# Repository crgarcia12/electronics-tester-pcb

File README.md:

# electronics-tester-pcb
A PCB to test fabrication

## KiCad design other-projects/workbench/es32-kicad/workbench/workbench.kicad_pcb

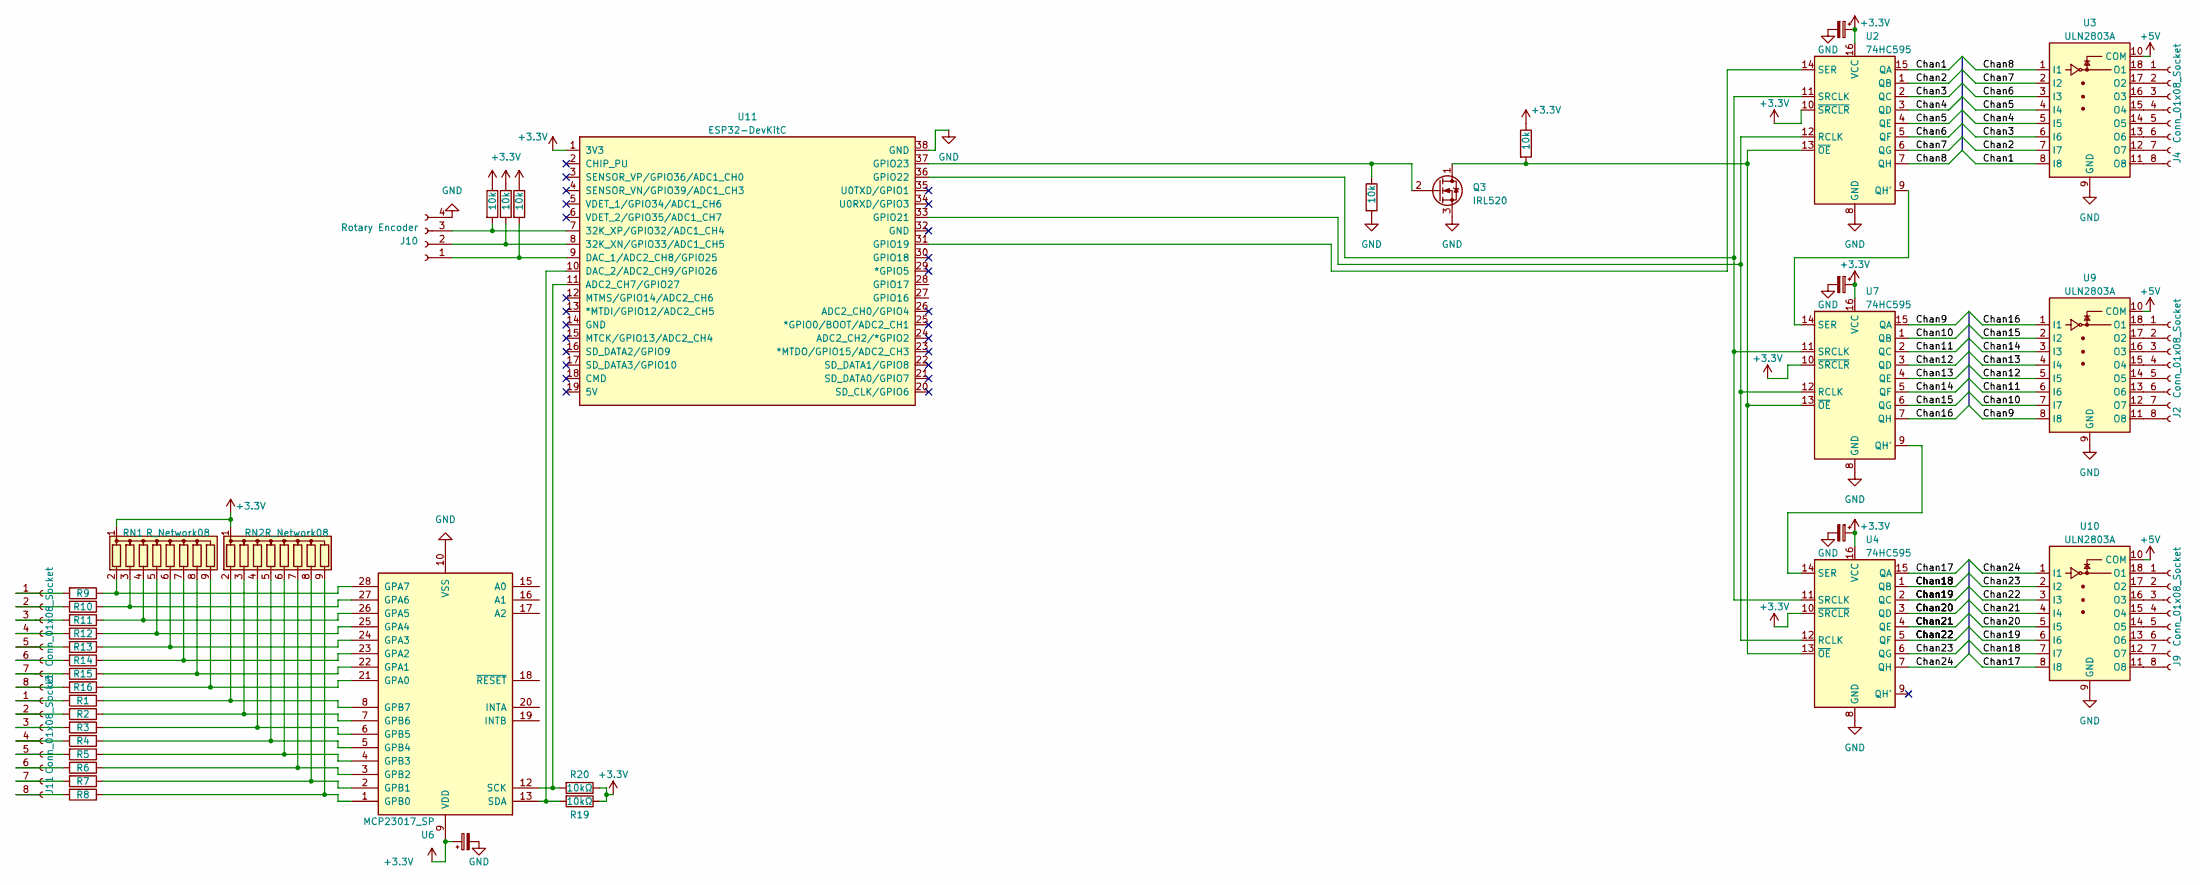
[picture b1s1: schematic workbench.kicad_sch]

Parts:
C14, C15, C16, C17: 10uF; CP_Radial_D6.3mm_P2.50mm
J2, J3, J4, J9, J11: Conn_01x08_Socket; PinSocket_1x08_P2.54mm_Vertical
J10: Rotary Encoder; JST_EH_B4B-EH-A_1x04_P2.50mm_Vertical
Q3: IRL520; TO-220-3_Vertical
R1, R2, R3, R4, R5, R6, R7, R8, R9, R10, R11, R12, R13, R14, R15, R16: R; R_Axial_DIN0207_L6.3mm_D2.5mm_P7.62mm_Horizontal
R19, R20: 10kΩ; R_Axial_DIN0207_L6.3mm_D2.5mm_P7.62mm_Horizontal; JLCPCB C25804
R21, R22, R35, R52, R53: 10k; R_Axial_DIN0207_L6.3mm_D2.5mm_P7.62mm_Horizontal
RN1, RN2: R_Network08; R_Array_SIP9
U2, U4, U7: 74HC595; DIP-16_W7.62mm_Socket_LongPads
U3, U9, U10: ULN2803A; DIP-18_W7.62mm_LongPads
U6: MCP23017_SP; DIP-28_W7.62mm
U11: ESP32-DevKitC

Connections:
+3.3V: C14.1, C15.1, C16.1, C17.1, R19.1, R20.1, R21.1, R22.1, R35.1, R53.1, RN1.1 (common), RN2.1 (common), U2.10 (~SRCLR), U2.16 (VCC), U4.10 (~SRCLR), U4.16 (VCC), U6.9 (VDD), U7.10 (~SRCLR), U7.16 (VCC), U11.1 (3V3)
+5V: U3.10 (COM), U9.10 (COM), U10.10 (COM)
/Chan1: U2.15 (QA), U3.8 (I8)
/Chan2: U2.1 (QB), U3.7 (I7)
/Chan3: U2.2 (QC), U3.6 (I6)
/Chan4: U2.3 (QD), U3.5 (I5)
/Chan5: U2.4 (QE), U3.4 (I4)
/Chan6: U2.5 (QF), U3.3 (I3)
/Chan7: U2.6 (QG), U3.2 (I2)
/Chan8: U2.7 (QH), U3.1 (I1)
/Chan9: U7.15 (QA), U9.8 (I8)
/Chan10: U7.1 (QB), U9.7 (I7)
/Chan11: U7.2 (QC), U9.6 (I6)
/Chan12: U7.3 (QD), U9.5 (I5)
/Chan13: U7.4 (QE), U9.4 (I4)
/Chan14: U7.5 (QF), U9.3 (I3)
/Chan15: U7.6 (QG), U9.2 (I2)
/Chan16: U7.7 (QH), U9.1 (I1)
/Chan17: U4.15 (QA), U10.8 (I8)
/Chan18: U4.1 (QB), U10.7 (I7)
/Chan19: U4.2 (QC), U10.6 (I6)
/Chan20: U4.3 (QD), U10.5 (I5)
/Chan21: U4.4 (QE), U10.4 (I4)
/Chan22: U4.5 (QF), U10.3 (I3)
/Chan23: U4.6 (QG), U10.2 (I2)
/Chan24: U4.7 (QH), U10.1 (I1)
GND: C14.2, C15.2, C16.2, C17.2, J10.4, Q3.3 (S), R52.2, U2.8 (GND), U3.9 (GND), U4.8 (GND), U6.10 (VSS), U7.8 (GND), U9.9 (GND), U10.9 (GND), U11.38 (GND)
unnamed: J2.1, U9.18 (O1)
unnamed: J2.2, U9.17 (O2)
unnamed: J2.3, U9.16 (O3)
unnamed: J2.4, U9.15 (O4)
unnamed: J2.5, U9.14 (O5)
unnamed: J2.6, U9.13 (O6)
unnamed: J2.7, U9.12 (O7)
unnamed: J2.8, U9.11 (O8)
unnamed: J3.1, R9.2
unnamed: J3.2, R10.2
unnamed: J3.3, R11.2
unnamed: J3.4, R12.2
unnamed: J3.5, R13.2
unnamed: J3.6, R14.2
unnamed: J3.7, R15.2
unnamed: J3.8, R16.2
unnamed: J4.1, U3.18 (O1)
unnamed: J4.2, U3.17 (O2)
unnamed: J4.3, U3.16 (O3)
unnamed: J4.4, U3.15 (O4)
unnamed: J4.5, U3.14 (O5)
unnamed: J4.6, U3.13 (O6)
unnamed: J4.7, U3.12 (O7)
unnamed: J4.8, U3.11 (O8)
unnamed: J9.1, U10.18 (O1)
unnamed: J9.2, U10.17 (O2)
unnamed: J9.3, U10.16 (O3)
unnamed: J9.4, U10.15 (O4)
unnamed: J9.5, U10.14 (O5)
unnamed: J9.6, U10.13 (O6)
unnamed: J9.7, U10.12 (O7)
unnamed: J9.8, U10.11 (O8)
unnamed: J10.1, R35.2, U11.9 (DAC_1/ADC2_CH8/GPIO25)
unnamed: J10.2, R22.2, U11.8 (32K_XN/GPIO33/ADC1_CH5)
unnamed: J10.3, R21.2, U11.7 (32K_XP/GPIO32/ADC1_CH4)
unnamed: J11.1, R1.2
unnamed: J11.2, R2.2
unnamed: J11.3, R3.2
unnamed: J11.4, R4.2
unnamed: J11.5, R5.2
unnamed: J11.6, R6.2
unnamed: J11.7, R7.2
unnamed: J11.8, R8.2
unnamed: Q3.1 (D), R53.2, U2.13 (~OE), U4.13 (~OE), U7.13 (~OE)
unnamed: Q3.2 (G), R52.1, U11.37 (GPIO23)
unnamed: R9.1, RN1.2 (R1), U6.28 (GPA7)
unnamed: R10.1, RN1.3 (R2), U6.27 (GPA6)
unnamed: R11.1, RN1.4 (R3), U6.26 (GPA5)
unnamed: R12.1, RN1.5 (R4), U6.25 (GPA4)
unnamed: R13.1, RN1.6 (R5), U6.24 (GPA3)
unnamed: R14.1, RN1.7 (R6), U6.23 (GPA2)
unnamed: R15.1, RN1.8 (R7), U6.22 (GPA1)
unnamed: R16.1, RN1.9 (R8), U6.21 (GPA0)
unnamed: R1.1, RN2.2 (R1), U6.8 (GPB7)
unnamed: R2.1, RN2.3 (R2), U6.7 (GPB6)
unnamed: R3.1, RN2.4 (R3), U6.6 (GPB5)
unnamed: R4.1, RN2.5 (R4), U6.5 (GPB4)
unnamed: R5.1, RN2.6 (R5), U6.4 (GPB3)
unnamed: R6.1, RN2.7 (R6), U6.3 (GPB2)
unnamed: R7.1, RN2.8 (R7), U6.2 (GPB1)
unnamed: R8.1, RN2.9 (R8), U6.1 (GPB0)
unnamed: U2.9 (QH'), U7.14 (SER)
unnamed: U4.14 (SER), U7.9 (QH')
unnamed: R20.2, U6.12 (SCK), U11.11 (ADC2_CH7/GPIO27)
unnamed: R19.2, U6.13 (SDA), U11.10 (DAC_2/ADC2_CH9/GPIO26)
unnamed: U2.14 (SER), U11.31 (GPIO19)
unnamed: U2.12 (RCLK), U4.12 (RCLK), U7.12 (RCLK), U11.33 (GPIO21)
unnamed: U2.11 (SRCLK), U4.11 (SRCLK), U7.11 (SRCLK), U11.36 (GPIO22)

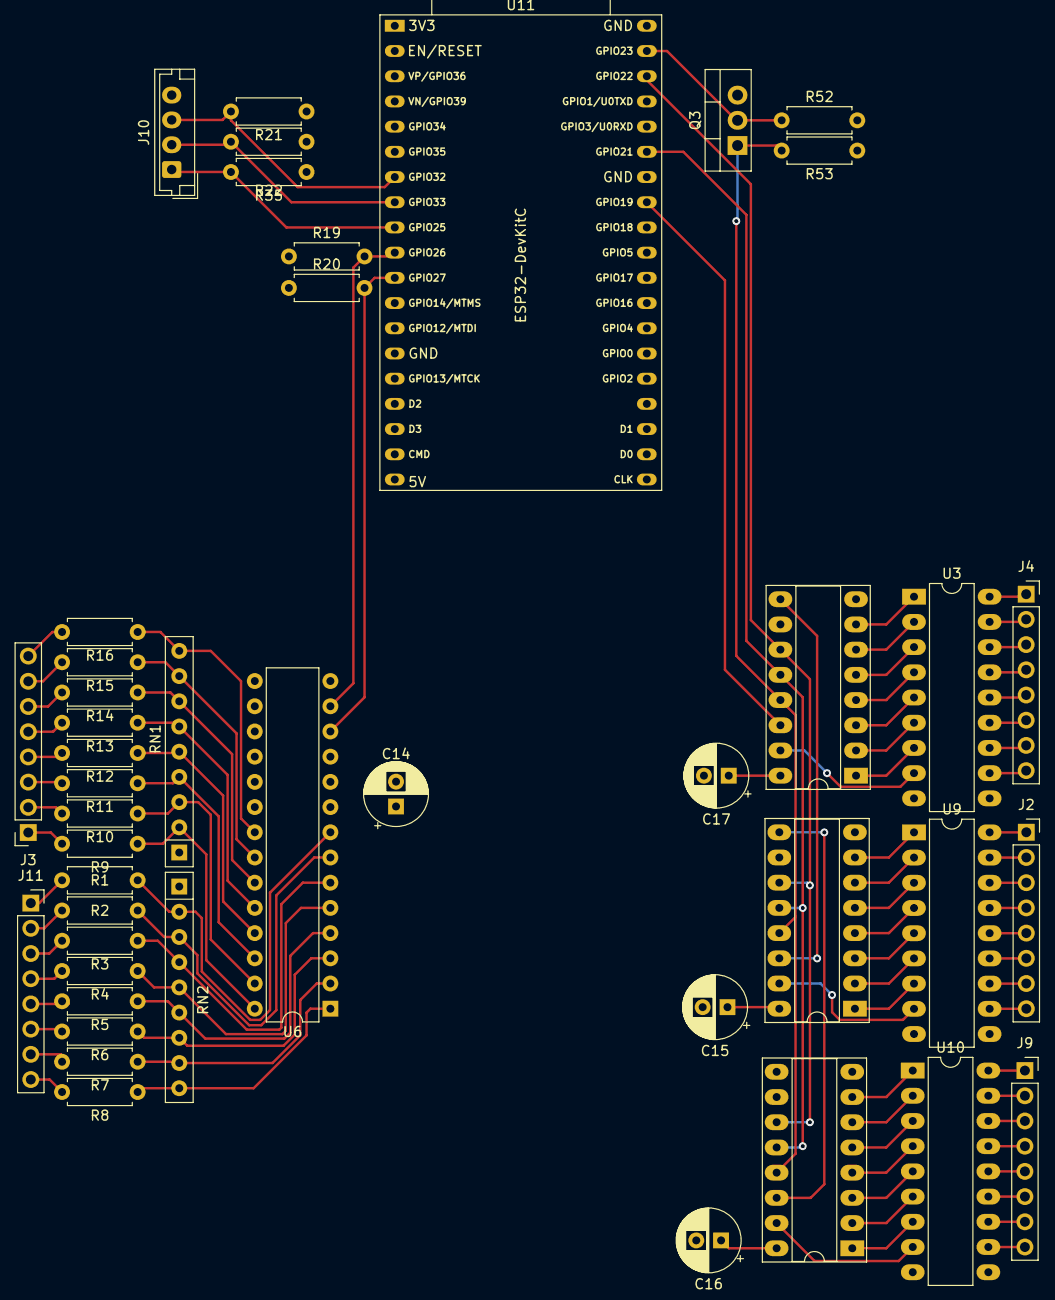
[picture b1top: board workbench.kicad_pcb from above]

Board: 4 copper layers, 44 parts (0 on the bottom side), 95 nets.

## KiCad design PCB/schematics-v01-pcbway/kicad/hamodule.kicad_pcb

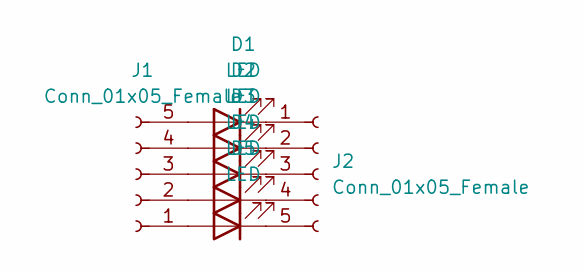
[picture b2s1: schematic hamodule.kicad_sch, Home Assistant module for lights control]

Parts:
D1, D2, D3, D4, D5: LED; LED_0805_2012Metric_Pad1.15x1.40mm_HandSolder
J1, J2: Conn_01x05_Female; PinSocket_1x05_P2.54mm_Vertical

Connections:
unnamed: D1.1 (K), J2.1
unnamed: D1.2 (A), J1.5
unnamed: D2.1 (K), J2.2
unnamed: D2.2 (A), J1.4
unnamed: D3.1 (K), J2.3
unnamed: D3.2 (A), J1.3
unnamed: D4.1 (K), J2.4
unnamed: D4.2 (A), J1.2
unnamed: D5.1 (K), J2.5
unnamed: D5.2 (A), J1.1

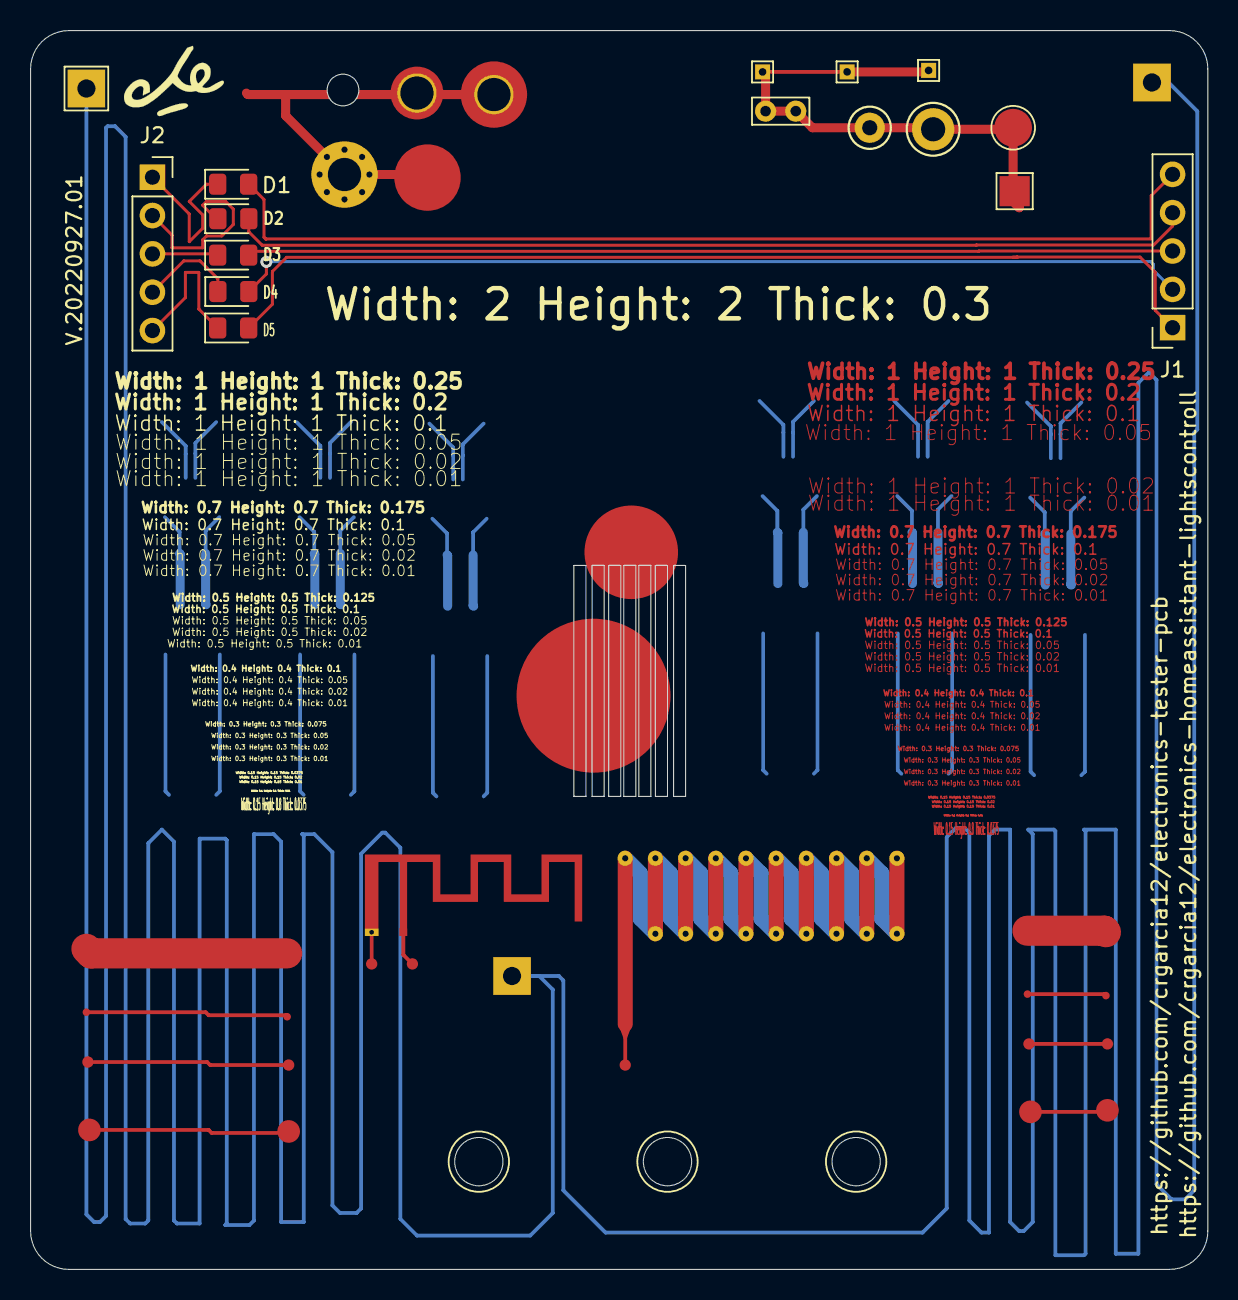
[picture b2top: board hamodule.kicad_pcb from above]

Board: 2 copper layers, 78.0 x 82.1 mm, 8 parts (0 on the bottom side), 10 nets.

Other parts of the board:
G1: LOGO; che

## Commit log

2022-09-26 initial PCB
2022-09-26 typo in silkscreen
2022-09-26 adding components
2022-09-27 [V01] github workflow
2022-09-27 [V01] removing old gerber
2022-09-27 renaming workflow
2022-09-27 [V01] Testing silkscreen
2022-09-27 [V01] Border silkscreen
2022-09-27 [Readme] Adding pictures
2022-09-28 removing **REF**
2022-09-28 [V01] extend solder mask
2022-09-28 [V01] readme images
2023-02-12 adding V2
2023-02-12 V2 iteration 1
2023-05-06 Adding workbench and LCD projects
2023-05-08 Working in the workbench
2023-05-23 workbench PCB update
2023-05-27 sending v02 to jlc
